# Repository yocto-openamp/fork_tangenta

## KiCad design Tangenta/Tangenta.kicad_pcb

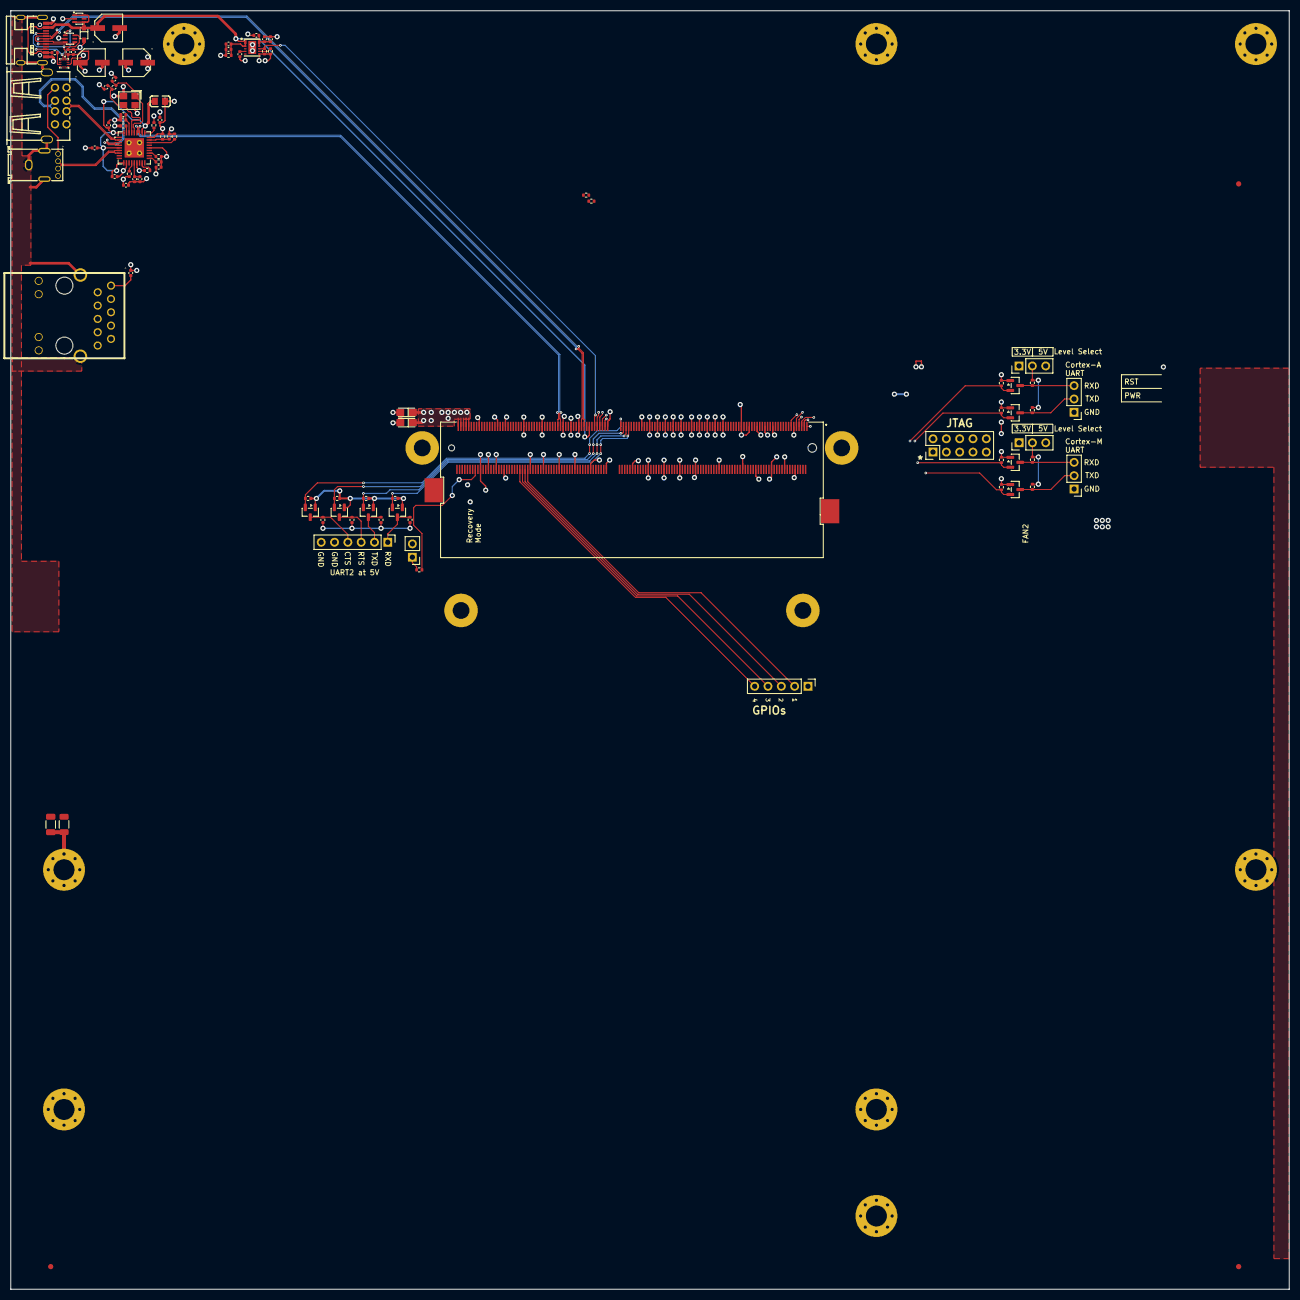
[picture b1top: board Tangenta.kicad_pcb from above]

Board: 4 copper layers, 243.8 x 243.8 mm, 105 parts (0 on the bottom side), 68 nets.

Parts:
C1: 2nF; C_1206_3216Metric
C40, C44, C50, C51, C52, C53, C54, C55, C57, C58, C63, C163: 100nF; C_0402_1005Metric
C41, C42, C43: 100uF; C_0402_1005Metric
C45: 10nF; C_0402_1005Metric
C46: 4.7uF; C_0402_1005Metric
C47: 1nF; C_0402_1005Metric
C48, C56, C59: 16CE47FSS; CAP_L5
C49, C62: 1uF; C_0402_1005Metric
C60, C61: 18pF; C_0402_1005Metric
C106, C107: 47uF; CAP_TANTAL_A
D5: BZT52C6V2S-7-F
FB1: GZ2012D101TF; Ferrite_Bead_100
FID1, FID2, FID3: Fiducial; Fiducial_1mm_Mask2mm
H1: MountingHole_Pad; MountingHole_4mm_Pad_Via
H2, H3, H4, H6, H7, H8, H9: MountingHole; MountingHole_4mm_Pad_Via
H12, H13, H14, H15: MountingHole; MountingHole_3.2mm_M3_Pad
J3: TYPEC-304-ACP16; USB_TYPEC
J4: 906-151A1058D10200; USB_VERTICAL_BLUE
J5: 907-211A1019D10200; USB_2_CONNECTOR
J11: 2309410-1; SODIMM_DDR4
J15: Conn_01x05_Pin; PinHeader_1x05_P2.54mm_Vertical
J16: Conn_01x02_Pin; PinHeader_1x02_P2.54mm_Vertical
J22: HY911130A; RJ45_MAGJACK_HY911130A
J27: Conn_01x06_Pin; PinHeader_1x06_P2.54mm_Vertical
J28, J29, J30, J31: Conn_01x03_Pin; PinHeader_1x03_P2.54mm_Vertical
J34: Conn_02x05_Odd_Even; PinHeader_2x05_P2.54mm_Vertical
Q11, Q12, Q13, Q14, Q15, Q16, Q17, Q18: BSS138; SOT-23
R1: 1k; R_1206_3216Metric
R27, R28, R31: 100k; R_0402_1005Metric
R29: 887k; R_0402_1005Metric
R30: 28.7k; R_0402_1005Metric
R32, R33, R35, R36, R37, R38, R40, R41: 10k; R_0402_1005Metric
R34: 12k; R_0402_1005Metric
R39: 1M; R_0402_1005Metric
R78: 330R; R_0402_1005Metric
R170, R171, R172, R173, R178, R179, R180, R181: 1.8k; R_0402_1005Metric
R174, R175, R176, R177, R182, R183, R184, R185: 4.7k; R_0402_1005Metric
U10: TUSB321RWBR
U11: AOZ1353DI-01; AOZ1353DI01
U12, U13: PUSB2X4Y-N; USB_ESD
U14: USB2514B-I_M2; USB_HUB
X1: X322524MOB4SI; XTAL_24MHZ

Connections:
/1V8: Q11.1 (G), Q12.1 (G), Q13.1 (G), Q14.1 (G), Q15.1 (G), Q16.1 (G), Q17.1 (G), Q18.1 (G), R27.2, R31.1, R170.2, R171.2, R172.2, R173.2, R178.2, R179.2, R180.2, R181.2
/3V3: C50.2, C52.2, C54.2, C59.1, FB1.1, J28.1, J29.1, R33.1, R37.1, R38.1, R40.1, R41.1, U14.15 (VDD33), U14.23 (VDD33), U14.27 (VBUS_DET)
/5V: C40.2, C41.2, C42.2, C43.2, C44.2, C56.1, C106.1, C107.1, J4.1 (VCC), J5.1 (VCC), J5.5 (VCC), J11.251, J11.253, J11.255, J11.257, J11.259, J28.3, J29.3, R174.2, R175.2, R176.2, R177.2, U10.12 (VDD), U11.10 (VIN), U11.12 (VIN)
/CHASSIS: C1.2, J3.13 (EP), J4.5 (SHELL), J4.6 (SHELL), J4.7 (SHELL), J5.9 (EH), J5.10 (EH), J22.15 (SH), J22.16 (SH), R1.1
/JTAG/JTAG.TCK: J11.9, J34.4
/JTAG/JTAG.TDI: J11.1, J34.8
/JTAG/JTAG.TDO: J11.5, J34.6
/JTAG/JTAG.TMS: J11.13, J34.2
/JTAG/JTAG.VREF: J11.7, J34.1
/JTAG/JTAG.nTRST: J11.3, J34.10
/Toradex/GPIO_1: J11.206, J15.2
/Toradex/GPIO_2: J11.208, J15.3
/Toradex/GPIO_3: J11.210, J15.4
/Toradex/GPIO_4: J11.212, J15.5
/Toradex/UART_2.CTS: J11.143, Q14.2 (S), R173.1
/Toradex/UART_2.RTS: J11.141, Q13.2 (S), R172.1
/Toradex/UART_2.RXD: J11.137, Q11.2 (S), R170.1
/Toradex/UART_2.TXD: J11.139, Q12.2 (S), R171.1
/Toradex/UART_3.RXD: J11.147, Q15.2 (S), R178.1
/Toradex/UART_3.TXD: J11.149, Q16.2 (S), R179.1
/Toradex/UART_4.RXD: J11.151, Q17.2 (S), R180.1
/Toradex/UART_4.TXD: J11.153, Q18.2 (S), R181.1
/Toradex/USB_DR.EN: J11.155, R28.2, U11.9 (EN)
/Toradex/USB_DR.ID: J11.161, R27.1, U10.9 (ID)
/Toradex/USB_DR.N: J3.A7 (D-), J3.B7 (D-), J11.163, U13.3
/Toradex/USB_DR.P: J3.A6 (D+), J3.B6 (D+), J11.165, U13.4
/Toradex/USB_DR.VBUS: C46.2, C47.2, C48.1, D5.1 (K), J3.A4B9 (VBUS), J3.B4A9 (VBUS), J11.159, R29.1, R32.2, U11.1 (VOUT), U11.3 (VOUT), U12.1, U12.3, U12.4, U12.6
/Toradex/USB_DR.nOC: J11.157, R31.2, U11.4 (FLTB)
/Toradex/USB_UP.N: J11.181, U14.30 (USBDM_UP)
/Toradex/USB_UP.P: J11.183, U14.31 (USBDP_UP)
/Toradex/nCTRL_REC: J11.246, R78.1
/UART_5V/CTS_2_H: J27.4, Q14.3 (D), R177.1
/UART_5V/RTS_2_H: J27.3, Q13.3 (D), R176.1
/UART_5V/RXD_2_H: J27.1, Q11.3 (D), R174.1
/UART_5V/TXD_2_H: J27.2, Q12.3 (D), R175.1
/UART_Terminal/U3_RXD: J30.3, Q15.3 (D), R182.1
/UART_Terminal/U3_TXD: J30.2, Q16.3 (D), R183.1
/UART_Terminal/U3_VSEL: J28.2, R182.2, R183.2
/UART_Terminal/U4_RXD: J31.3, Q17.3 (D), R184.1
/UART_Terminal/U4_TXD: J31.2, Q18.3 (D), R185.1
/UART_Terminal/U4_VSEL: J29.2, R184.2, R185.2
/USB/3V3A: C55.2, C57.2, C58.2, FB1.2, U14.5 (VDDA33), U14.10 (VDDA33), U14.29 (VDDA33), U14.36 (VDDA33)
/USB/USB_D1_N: J5.2 (D1-), U14.1 (USBDM_DN1/PRT_DIS_M1)
/USB/USB_D1_P: J5.3 (D1+), U14.2 (USBDP_DN1/PRT_DIS_P1)
/USB/USB_D2_N: J5.6 (D2-), U14.3 (USBDM_DN2/PRT_DIS_M2)
/USB/USB_D2_P: J5.7 (D2+), U14.4 (USBDP_DN2/PRT_DIS_P2)
/USB/USB_D3_N: J4.2 (D-), U14.6 (USBDM_DN3/PRT_DIS_M3)
/USB/USB_D3_P: J4.3 (D+), U14.7 (USBDP_DN3/PRT_DIS_P3)
/USB/XTALIN: C60.2, R39.1, U14.33 (XTALIN/CLKIN), X1.3 (OSC2)
/USB/XTALOUT: C61.2, R39.2, U14.32 (XTALOUT), X1.1 (OSC1)
/USB_DR/USB_DR_CC1: J3.A5 (CC1), U10.1 (CC1), U13.6
/USB_DR/USB_DR_CC2: J3.B5 (CC2), U10.2 (CC2), U13.1
GNDREF: C1.1, C40.1, C41.1, C42.1, C43.1, C44.1, C45.1, C46.1, C47.1, C48.2, C49.1, C50.1, C51.1, C52.1, C53.1, C54.1, C55.1, C56.2, C57.1, C58.1, C59.2, C60.1, C61.1, C62.1, C63.1, C106.2, C107.2, C163.2, D5.2 (A), H1.1 (1_1), J3.A1B12 (GND), J3.B1A12 (GND), J4.4 (GND), J5.4 (GND), J5.8 (GND), J11.10, J11.11, J11.18, J11.27, J11.28, J11.33, J11.39, J11.40, J11.45, J11.50, J11.51, J11.65, J11.68, J11.71, J11.77, J11.83, J11.86, J11.89, J11.97, J11.98, J11.103, J11.109, J11.110, J11.115, J11.121, J11.122, J11.127, J11.134, J11.145, J11.146, J11.158, J11.167, J11.170, J11.173, J11.179, J11.182, J11.194, J11.195, J11.204, J11.209, J11.223, J11.224, J11.229, J11.230, J11.236, J11.242, J11.243, J15.1, J16.2, J22.10, J22.12, J22.13, J27.5, J27.6, J30.1, J31.1, J34.3, J34.5, R1.2, R28.1, R30.1, R32.1, R34.1, R35.1, R36.1, U10.10 (GND), U11.7 (GND), U11.13 (EP), U12.2 (GND), U13.2 (GND), U14.11 (TEST), U14.37 (EP), X1.2 (GND), X1.4 (GND)
unnamed: C163.1, J22.1
unnamed: J16.1, R78.2
unnamed: R29.2, U10.5 (VBUS_DET)
unnamed: R30.2, U11.8 (ILIM)
unnamed: C45.2, U11.5 (SS)
unnamed: C62.2, C63.2, U14.14 (CRFILT)
unnamed: R36.2, U14.25 (HS_IND/CFG_SEL1)
unnamed: R40.2, U14.13 (OCS_N1)
unnamed: R41.2, U14.17 (OCS_N2)
unnamed: R38.2, U14.19 (OCS_N3)
unnamed: R37.2, U14.21 (OCS_N4)
unnamed: C49.2, C51.2, U14.34 (PLLFILT)
unnamed: R34.2, U14.35 (RBIAS)
unnamed: C53.2, R33.2, U14.26 (RESET_N)
unnamed: R35.2, U14.28 (SUSP_IND/LOCAL_PWR/NON_REM0)
